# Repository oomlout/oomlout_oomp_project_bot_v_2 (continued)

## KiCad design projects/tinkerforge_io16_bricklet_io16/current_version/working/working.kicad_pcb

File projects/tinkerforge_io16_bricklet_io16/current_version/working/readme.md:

# io16_bricklet
 
## summary 
* id: tinkerforge_io16_bricklet_io16
* user: tinkerforge
* name: io16_bricklet
* board: io16
* repo: https://github.com/Tinkerforge/io16-bricklet
* src_file_repo_kicad_pcb: hardware/io16.kicad_pcb
* src_file_repo_kicad_pcb_link: https://github.com/Tinkerforge/io16-bricklet/tree/master/hardware/io16.kicad_pcb

* src_file_repo_sch: hardware/io16.sch
* src_file_repo_sch_link: https://github.com/Tinkerforge/io16-bricklet/tree/master/hardware/io16.sch
* full details link: https://github.com/oomlout/oomlout_oomp_project_bot_v_2/tree/main/projects/tinkerforge_io16_bricklet_io16/current_version/working

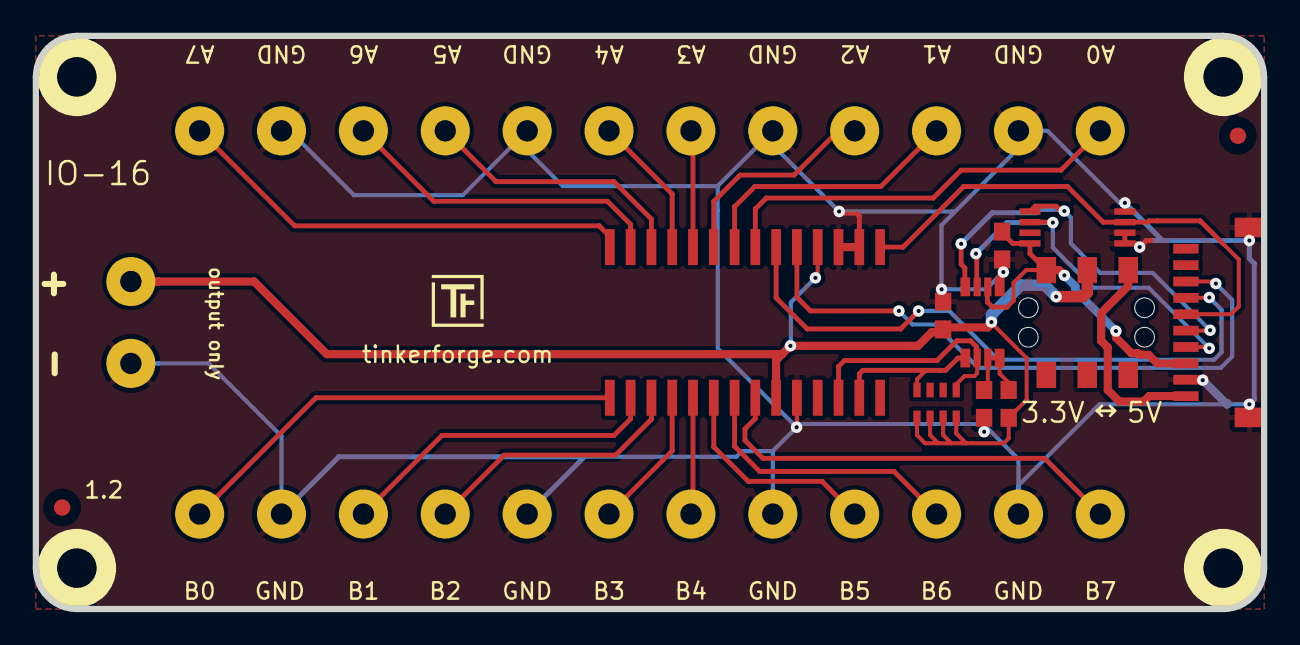
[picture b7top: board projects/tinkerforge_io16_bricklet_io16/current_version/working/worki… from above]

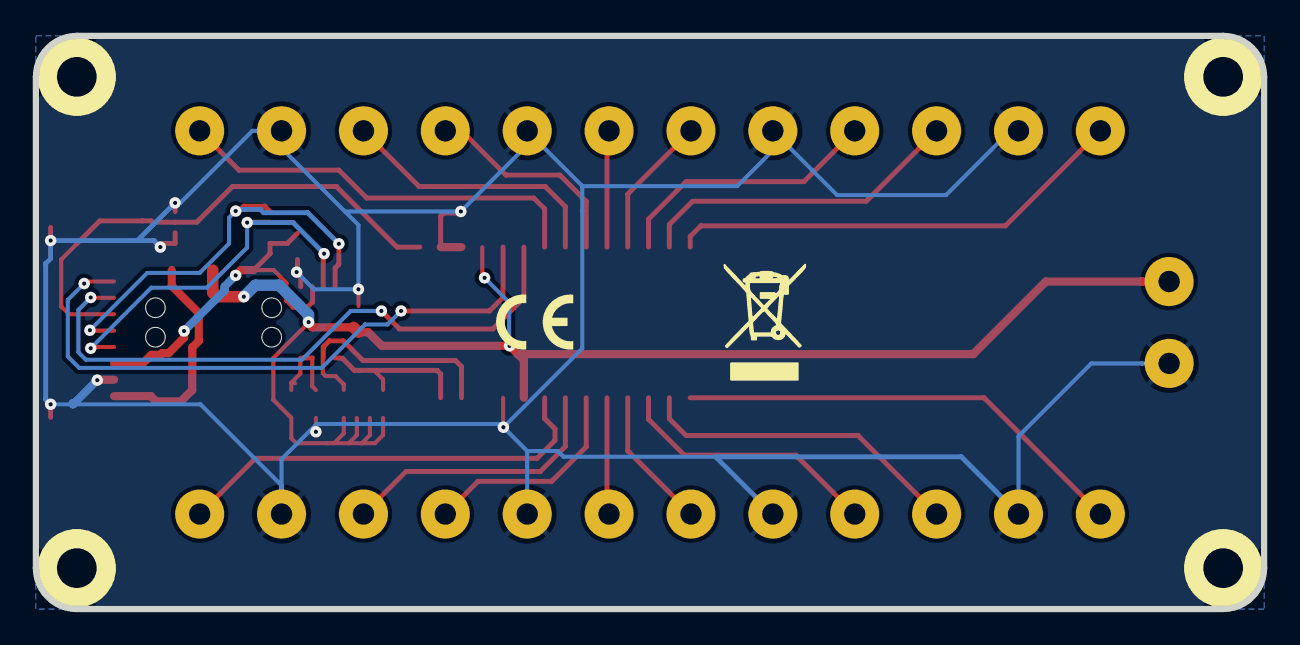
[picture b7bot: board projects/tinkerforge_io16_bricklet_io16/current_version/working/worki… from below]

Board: 2 copper layers, 75.0 x 35.0 mm, 32 parts (2 on the bottom side), 28 nets.

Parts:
C1, C2, C3: 100nF; C0603E
Fiducial_Mark: VAL**; Fiducial_Mark
Fiducial_Mark#2: VAL**; Fiducial_Mark
J1, J2, J3, J4, J5, J6, J7, J8, J9, J10, J11, J12, J13: AKL_5_2
P1: CON-SENSOR
R1: 200k; R0603E
RP1: 4.7k; 4X0603
Ref**: Val**; Logo_31x31
SW1: Power_Select; SLIDE_SWITCH
U1: M24C64; TSSOP8
U2: MCP23017; SOIC28
U3: PCA9306; TSSOP8_3
U4, U5, U6, U7: DRILL; DRILL_NP
VAL: WEEE_7mm
VAL#2: CE_5mm

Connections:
GND: C1.1, C2.2, C3.2, J1.1, J2.1, J4.2, J5.1, J7.2, J8.2, J10.1, J11.2, J13.1, P1.2, P1.EP, U1.1, U1.2, U1.4, U2.10, U2.16, U2.17, U3.1
IN_1: P1.7, U2.20
IN_2: P1.8, U2.19
unnamed: C3.1, R1.2, U3.7, U3.8
unnamed: J2.2, U2.1
unnamed: J3.1, U2.3
unnamed: J3.2, U2.2
unnamed: J4.1, U2.4
unnamed: J5.2, U2.5
unnamed: J6.1, U2.7
unnamed: J6.2, U2.6
unnamed: J7.1, U2.8
unnamed: J8.1, U2.28
unnamed: J9.1, U2.27
unnamed: J9.2, U2.26
unnamed: J10.2, U2.25
unnamed: J11.1, U2.24
unnamed: J12.1, U2.23
unnamed: J12.2, U2.22
unnamed: J13.2, U2.21
unnamed: P1.1, SW1.1
SCL: P1.4, U1.6, U3.3
SCL2: RP1.8, U2.12, U3.6
SDA: P1.5, U1.5, U3.4
SDA2: RP1.5, U2.13, U3.5
SEL: P1.6, U1.3, U2.15
VAA: C2.1, J1.2, R1.1, RP1.1, RP1.2, RP1.3, RP1.4, SW1.2, U2.9, U2.18
VCC: C1.2, P1.3, SW1.3, U1.8, U3.2

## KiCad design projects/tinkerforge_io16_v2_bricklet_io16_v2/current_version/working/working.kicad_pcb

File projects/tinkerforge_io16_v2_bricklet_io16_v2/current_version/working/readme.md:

# io16_v2_bricklet
 
## summary 
* id: tinkerforge_io16_v2_bricklet_io16_v2
* user: tinkerforge
* name: io16_v2_bricklet
* board: io16_v2
* repo: https://github.com/Tinkerforge/io16-v2-bricklet
* src_file_repo_kicad_pcb: hardware/io16-v2.kicad_pcb
* src_file_repo_kicad_pcb_link: https://github.com/Tinkerforge/io16-v2-bricklet/tree/master/hardware/io16-v2.kicad_pcb

* src_file_repo_sch: hardware/io16-v2.sch
* src_file_repo_sch_link: https://github.com/Tinkerforge/io16-v2-bricklet/tree/master/hardware/io16-v2.sch
* full details link: https://github.com/oomlout/oomlout_oomp_project_bot_v_2/tree/main/projects/tinkerforge_io16_v2_bricklet_io16_v2/current_version/working

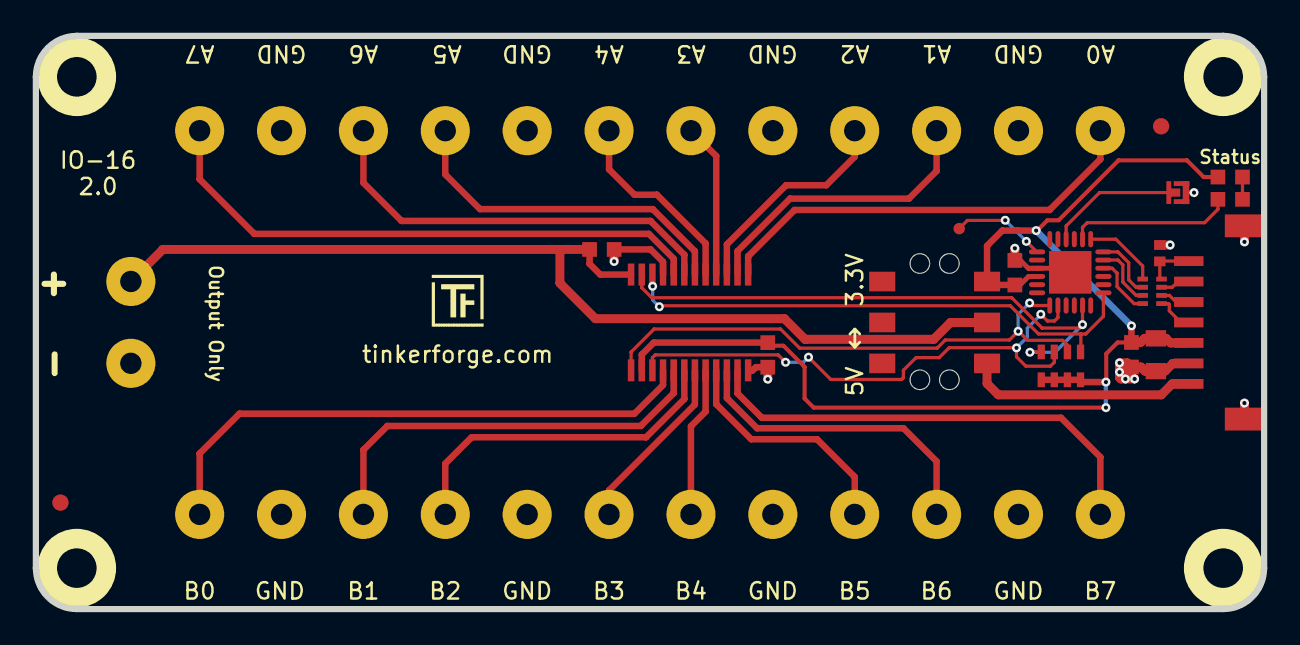
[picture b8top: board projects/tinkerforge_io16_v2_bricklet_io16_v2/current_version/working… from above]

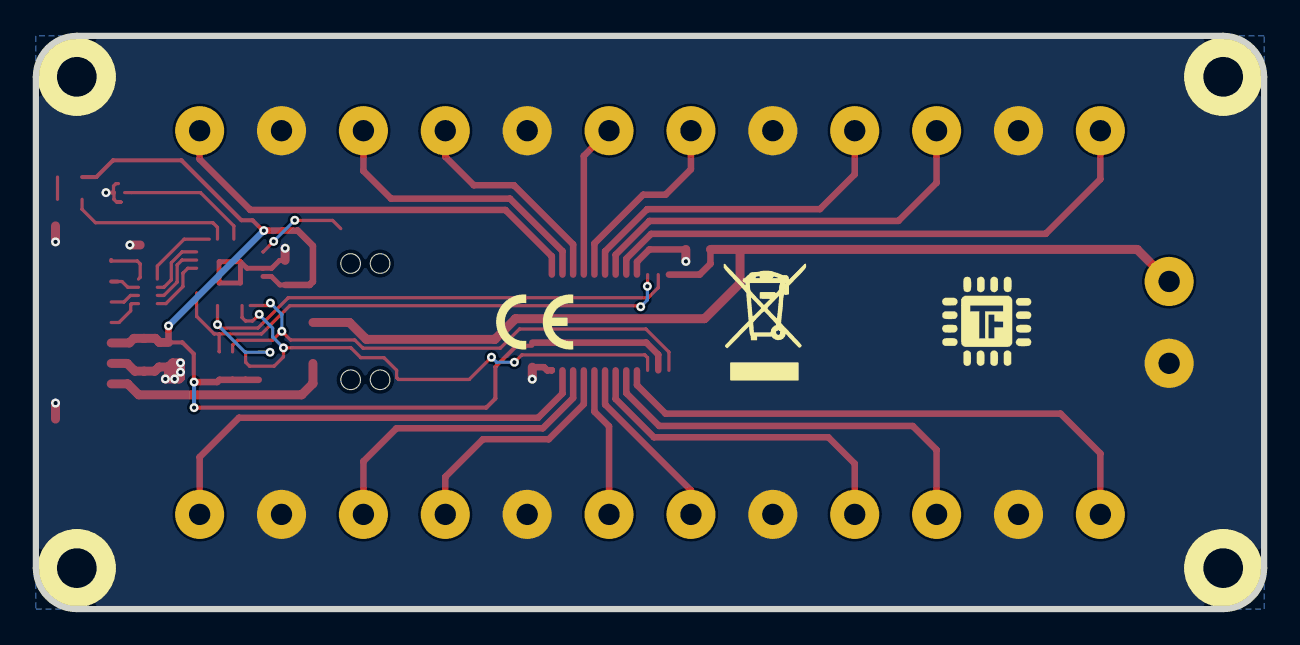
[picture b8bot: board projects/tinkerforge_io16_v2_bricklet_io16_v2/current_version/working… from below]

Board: 2 copper layers, 75.0 x 35.0 mm, 38 parts (2 on the bottom side), 36 nets.

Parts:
C1: 10uF; C0805
C2, C3, C6: 100nF; C0603F
C4: 220pF; C0402F
C5: 1uF; C0603F
D1: blue; D0603F
Fiducial_Mark: VAL**; Fiducial_Mark
Fiducial_Mark#2: VAL**; Fiducial_Mark
J1, J2, J3, J4, J5, J6, J7, J8, J9, J10, J11, J12, J13: AKL_5_2
P1: CON-SENSOR2
P2: DEBUG; DEBUG_PAD
P3: BOOT; SolderJumper
R1: 1k; R0603F
RP1: 2k2; 4X0603
RP2: 82; 4X0402
Ref**: Val**; Logo_31x31
SW1: Power_Select; SLIDE_SWITCH
U1: XMC1100; QFN24-4x4mm-0.5mm
U4, U5, U6, U7: DRILL; DRILL_NP
U8: PCAL6416APW; TSSOP24-44
VAL: WEEE_7mm
VAL#2: CE_5mm

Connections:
+5V: P1.1, SW1.1
GND: C1.2, C2.2, C3.1, C4.2, C5.2, C6.2, J1.1, J2.1, J4.2, J5.1, J7.2, J8.2, J10.1, J11.2, J13.1, P1.2, P1.EP, P3.1, U1.9, U1.EXP, U8.12, U8.21
INT: RP1.7, U1.13, U8.1
unnamed: C4.1, P1.7, RP2.4
unnamed: D1.2, R1.2
unnamed: J2.2, U8.4
unnamed: J3.1, U8.6
unnamed: J3.2, U8.5
unnamed: J4.1, U8.7
unnamed: J5.2, U8.8
unnamed: J6.1, U8.10
unnamed: J6.2, U8.9
unnamed: J7.1, U8.11
unnamed: J8.1, U8.20
unnamed: J9.1, U8.19
unnamed: J9.2, U8.18
unnamed: J10.2, U8.17
unnamed: J11.1, U8.16
unnamed: J12.1, U8.15
unnamed: J12.2, U8.14
unnamed: J13.2, U8.13
unnamed: P1.4, RP2.1
unnamed: P1.5, RP2.2
unnamed: P1.6, RP2.3
unnamed: P2.1, U1.7
unnamed: P3.2, U1.4
unnamed: R1.1, U1.2
RESET: RP1.6, U1.14, U8.3
S-CLK: RP2.7, U1.23
S-CS: RP2.8, U1.22
S-MISO: RP2.5, U1.1
S-MOSI: RP2.6, U1.24
SCL: RP1.8, U1.19, U8.22
SDA: RP1.5, U1.17, U8.23
VAA: C3.2, J1.2, SW1.2, U8.24
VCC: C1.1, C2.1, C5.1, C6.1, D1.1, P1.3, RP1.1, RP1.2, RP1.3, RP1.4, SW1.3, U1.10, U8.2
